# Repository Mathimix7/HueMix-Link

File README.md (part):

<h1 align="center">HueMix-Link</h1>

## Table of Contents

- [Quick Start](#quick-start)
- [Project Overview](#project-overview)
- [Screenshots](#screenshots)
- [What Is In This Repository](#what-is-in-this-repository)
- [System Overview](#system-overview)
- [Prerequisites](#prerequisites)
- [Installation](#installation)
- [First-time Commissioning Workflow](#first-time-commissioning-workflow)
- [ESP Firmware: Build and Flash](#esp-firmware-build-and-flash)
- [Firmware Updates (OTA Page)](#firmware-updates-ota-page)
- [Configuration and Data Storage](#configuration-and-data-storage)
- [Networking and Ports](#networking-and-ports)
- [How Automation Works](#how-automation-works)
- [Devices](#devices)
- [License](#license)

## Quick Start

1. Install the backend on a Linux host:

 ```bash
  git clone https://github.com/Mathimix7/HueMix-Link.git
  cd HueMix-Link
  sudo bash install.sh
  ```

2. Open the web UI at `http://huemixlink.local` or your server IP.
2. Pair your Hue Bridge from the Bridge configuration page.
3. Put an ESP device into pairing mode and add it from the Pairing page.
4. Configure the device behavior, then verify it by triggering a button, motion sensor, or lightstrip sync.

## Project Overview

HueMix-Link is a local smart home bridge that connects custom ESP-based devices (gateways, buttons, remotes, motion sensors, door sensors, and lightstrips) to Philips Hue rooms and scenes.

It provides:

- A Flask web UI for setup and management
- A UDP server for low-latency gateway communication
- Automation logic for buttons, remotes, and motion sensors
- OTA firmware update workflows for all device types
- Backup and restore tools for configuration data

## Screenshots

<table width="85%" align="center">
  <tr>
    <td colspan="2" align="center">
      
    </td>
  </tr>
  <tr>
    <td width="50%" align="center">
      
    </td>
    <td width="50%" align="center">
      
    </td>
  </tr>
  <tr>
    <td width="50%" align="center">
      
    </td>
    <td width="50%" align="center">
      
    </td>
  </tr>
</table>

## What Is In This Repository

- `python/`: Main backend service (Flask UI + UDP network + automations + OTA)
- `esp-firmware/`: PlatformIO firmware sources for all device types (gateway, buttons, remotes, motion sensors, door sensors, lightstrips)
- `Hardware-designs/`: KiCad design files for all device types (gateway, buttons, remotes, motion sensors, door sensors, lightstrips)
- `3D Files/`: 3D model files for all device types (STL format for 3D printing)
- `install.sh`: Linux installer/updater
- `VERSION`: Version file for installer/update workflows

## System Overview

### High-level architecture

1. **All ESP devices use ESP-NOW**: Low-power mesh protocol for device-to-device communication
2. **Gateways bridge ESP-NOW to UDP**: Gateways receive ESP-NOW messages and forward them to the backend via UDP
3. **Backend (UDP server) receives events**: Button presses, remote actions, motion detections, device hellos, delivery reports
4. **Automation engine maps events to Hue actions**: Scene activation, toggle on/off, brightness adjust, and lightstrip sync
5. **Hue state is cached and synchronized**: Automations and lightstrips stay aligned with current room/scene state
6. **Web UI for management**: Device pairing, automation configuration, OTA updates, monitoring, and backups

### Main runtime services

- **Flask + Waitress**: Web UI server `127.0.0.1:5001` (default)
- **UDP listener**: Receives gateway messages on `0.0.0.0:7777` (default, configurable)
- **Automation service**: Listens to device events and Hue state changes, applies configured logic
- **OTA manager**: Handles firmware distribution, chunking, and acknowledgment tracking

## Prerequisites

### Software

- Python 3.9+ (3.10+ recommended)
- `pip` and virtual environment support (`venv`)
- Network access to your Hue Bridge (same LAN)
- Linux OS with `systemd` (for production install)
- `sudo` access and `apt` package manager

### Hardware

- At least one Hue Bridge with configured rooms/scenes
- Supported HueMix-Link devices (gateways, buttons, remotes, motion sensors, door sensors, lightstrips)
- Firmware binaries matching your device type and model

## Installation

### Linux

From the repository root:

```bash
sudo bash install.sh
```

The installer will:

- Deploy the Python app to `/opt/huemix-link`
- Create a dedicated service user and Python virtual environment
- Set up a `systemd` service (`huemix-link`) to run on boot
- Configure HAProxy to expose the web app (HTTP port 80, HTTPS port 443 by default)
- Store all runtime data in `/opt/huemix-link/data`

Useful installer options:

```bash
sudo bash install.sh --help           # Show all options
sudo bash install.sh --yes            # Non-interactive install
sudo bash install.sh --dry-run        # Preview without making changes
sudo bash install.sh --force          # Force recreation of venv
sudo bash install.sh --show-version   # Show installed and source versions
sudo bash install.sh --port 8080      # Expose on custom HTTP port
sudo bash install.sh --no-https       # Disable HTTPS (HTTP only)
sudo bash install.sh --no-local       # Skip huemixlink.local hostname setup
```

After installation, the web UI is accessible at:

- `https://huemixlink.local` (or your server IP)
- `http://huemixlink.local` (or your server IP)

### Updating

To update the backend to a newer version, pull the latest code and re-run the installer:

```bash
git pull
sudo bash install.sh
```

The installer detects the existing installation, updates the files, and restarts the service automatically.

## First-time Commissioning Workflow

1. **Start the backend** (automatic on boot if installed via installer)
2. **Open the web UI** at `http://huemixlink.local` (or your server IP)
3. **Configure Hue Bridge**:
   - Go to the Bridge configuration page
   - Auto-discover or enter bridge IP manually
   - Press the Hue Bridge link button
   - Pair app with bridge (saves credentials)
4. **Pair ESP devices**:
   - Go to Pairing page
   - Start pairing window (choose device type if desired)
   - Power on or reset target devices
   - Devices announce themselves via ESP-NOW → gateway → backend
5. **Configure each device**:
    - **Buttons/Remotes**: Map to room + scenes + action behavior (normal, toggle, brightness, scene-cycle)
    - **Motion Sensors**: Set room, time slots, motion actions, after-actions, cooldown periods
    - **Door Sensors**: Set room, open/close actions, and any automation triggers tied to magnetic state changes
    - **Lightstrips**: Assign room, configure LED count/type, optional color scene overrides
    - **Gateways**: Verify online status, mesh routing, LED schedule (day/night auto-off)
6. **Validate behavior** by triggering physical events and checking Hue room/scene changes

## ESP Firmware: Build and Flash

### Flashing ESP devices

**Option 1: Serial flash via OTA page**

1. Go to the **OTA** page in the web UI
2. Select firmware type
3. Connect ESP device via serial in programming mode
4. Click **Flash** and select serial port
5. Monitor progress on the page

**Option 2: Serial port flash**

Use PlatformIO to flash directly via USB:

```bash
cd esp-firmware
pio run -e esp32_net_node --target upload
```

Or use `esptool.py` directly:

```bash
esptool.py --port /dev/ttyUSB0 write_flash 0x0 huemixlink-esp32-net-vX.Y.Z.bin
```

Pre-built firmware binaries are available in the project's GitHub releases. Download the `.bin` file(s) matching your device type and platform.

## Firmware Updates (OTA Page)

The **OTA** page in the web UI lets you:

- **Check available versions** from GitHub releases
- **Select device** type/model and target device
- **Battery-powered devices**: double-press the reset button before OTA update
- **Initiate flash** with progress monitoring
- **Monitor errors** and retry failed updates

## Configuration and Data Storage

All runtime configuration is stored in `python/data/` (or `/opt/huemix-link/data` in production) as JSON files:

- `bridge.json`: Hue bridge IP and app username
- `config.json`: Server settings (UDP port, dev mode)
- `gateways.json`: Known gateway devices
- `buttons.json`: Button and remote configurations
- `motion_sensors.json`: Motion sensor configurations and time slots
- `lightstrips.json`: Lightstrip configurations and color overrides
- `pairing_history.json`: Last 5 paired devices
- `home_id`: Unique identifier for this HueMix-Link instance. This value is embedded in every packet as a shared secret and used to verify that incoming messages belong to your installation. All devices must be paired while this ID is set — re-pairing is required if it changes.

Backups are created and restored through the settings page; they are stored in `data/backups/`.

## Networking and Ports

- **Web server (internal)**: `127.0.0.1:5001` (Flask)
- **UDP listener (internal)**: `0.0.0.0:7777` (default, receives gateway messages)
- **External HTTP/HTTPS (production)**: Exposed by HAProxy (default HTTP 80 + HTTPS 443)

UDP port can be changed in settings; the backend will restart UDP listening with the new port.

## How Automation Works

1. **Device sends event** via **ESP-NOW** (button press, remote action, motion detection)
2. **Gateway receives** via ESP-NOW and forwards message to backend via **UDP**
3. **UDP server** decodes and validates packet (signature check using HomeID)
4. **Device manager** resolves device identity; **pairing manager** verifies eligibility
5. **Automation engine** applies configured logic:
   - **Buttons/Remotes**: Scene cycle, toggle, brightness adjust, hold-to-adjust
   - **Motion Sensors**: Trigger scenes/lights on detection; post-motion fade/off actions; cooldown throttling
6. **Hue API** is called to apply scene/room/light changes
7. **Hue state manager** caches current room, light, and scene state
8. **Lightstrip sync**: Checks if any lightstrips should mirror current scene; sends raw LED commands via **ESP-NOW → gateway → UDP**

On startup, config sync reconciles saved room/scene references against live Hue topology to avoid stale mappings.

## Devices

### Gateway

<table><tr>
  <td></td>
  <td></td>
</tr></table>

The Gateway is a single board that contains two ESP32 modules working together:

- **Net Node** — connects to your home WiFi and bridges between the backend (UDP) and the ESP-NOW mesh. Runs WiFiManager for wireless configuration and relays commands to the radio node over a high-speed UART link.
- **Radio Node** — handles all ESP-NOW communication with peripheral devices (buttons, remotes, sensors, lightstrips) and forwards packets to/from the net node over UART. Extends ESP-NOW coverage independently of WiFi.

**LED indicators**

| LED | State | Meaning |
|-----|-------|---------|
| WiFi | Off | No power / booting |
| WiFi | Fast blink (0.2s) | Not yet configured — WiFi config portal is open |
| WiFi | Slow blink (0.5s) | Connecting or retrying WiFi |
| WiFi | Solid on | Online and operational |
| Data | Brief flash | Packet received or forwarded |
| Data | Breathing (fade in/out) | Net node OTA firmware update in progress |
| Radio | Brief flash | ESP-NOW packet relayed |
| Radio | Breathing (fade in/out) | Radio node OTA firmware update in progress |

**Buttons**

- **Main button**: Acts as a single button that can be mapped to a Hue room in the web UI
- **Aux button**: Hold 5+ seconds to factory-reset and re-open the WiFi config portal

**Initial setup**

1. Power on the gateway — the WiFi LED fast-blinks and it broadcasts SSID `HueMix Link - XXXXXXXX`
2. Connect to that SSID (password: `HueMixLink`) with a phone or laptop
3. Enter your home WiFi credentials and the backend server IP + UDP port
4. The gateway connects, the WiFi LED goes solid, and it sends a HELLO to the backend

**Pairing**

Gateways pair automatically once configured.

**OTA**

Both nodes are updated from the OTA page. Gateways receive OTA directly (no double-press needed).

---

### Radio Gateway (Serial Python)

The Radio Gateway can also run as a serial-connected ESP32 node that pairs with the Python backend instead of WiFi.

- **Net/host side**: Python maintains the gateway state, serial transport, OTA scheduling, and dashboard telemetry
- **Radio side**: ESP32 radio node handles ESP-NOW traffic, OLED status display, and forwards packets over UART
- **LED indicators**: Follows the configured gateway LED schedule; the OLED display also respects the same on/off timing
- **OTA**: Updated from the OTA page using the `gateway_radio_python` firmware target

**Setup**

1. Flash the `esp32_radio_python` firmware
2. Connect the radio node to the backend host over USB serial
3. Configure the serial port in the web UI
4. The backend will sync HOME_ID, gateway state, and dashboard telemetry automatically

---

### Button

<table><tr>
  <td></td>
  <td></td>
</tr></table>

The Button is a single pushbutton device that sends click, hold, and release events via ESP-NOW. The ESP32 version is battery-powered and deep-sleeps between presses, while the ESP8266 version is always-on and runs continuously.

> [!WARNING]
> The `normal_button` firmware is deprecated. The ESP32 Normal Button board v3 and later should use the `remote_button` firmware configured as 1, 2, or 3 buttons.

**Events sent**

| Action | Trigger |
|--------|---------|
| Click | Short press and release |
| Holding | Held beyond 500 ms, repeated every 500 ms |
| Release | Released after a hold |

**Default automation** (configurable in web UI): Click cycles scenes in the assigned room. Hold adjusts brightness. Release stops brightness adjustment.

**LED indicators**

| State | Meaning |
|-------|---------|
| Brief flash | Action sent via ESP-NOW |
| 2 fast blinks | No acknowledgment — gateway may be out of range |
| 2 slow blinks | Failed to pair device |
| 3 blinks | OTA mode |
| 5 blinks | Device powered on |
| Breathing | OTA in progress |

**Setup and pairing**

1. Flash firmware via serial or the OTA page
2. Open the Pairing page, start a pairing window, then press the button to wake the device
3. After pairing, assign the button to a room in the device settings

**OTA**

**Double-press the reset button** to enter OTA mode — the LED will blink 3 times to confirm. Then initiate the flash from the OTA page.

---

### Remote

<table><tr>
  <td></td>
  <td></td>
</tr></table>

The Remote is a battery-powered ESP32 device with up to 4 independently configurable buttons. Each button can target a different room with its own action type. The number of active buttons (1–4) is configured via hardware at flash time.

**Action types per button** (configurable in web UI)

| Type | Click | Hold |
|------|-------|------|
| Normal | Cycle scenes / turn room off | Adjust brightness |
| Toggle | Toggle room on/off | — |
| Brightness Up | Increase brightness | Increase continuously |
| Brightness Down | Decrease brightness | Decrease continuously |
| Scene Cycle | Cycle scenes (no off) | Adjust brightness |

**LED indicators**

| State | Meaning |
|-------|---------|
| Brief flash | Button action sent |
| 2 fast blinks | No acknowledgment — gateway may be out of range |
| 2 slow blinks | Failed to pair device |
| 3 blinks | OTA mode |
| 5 blinks | Device powered on |
| On 2 seconds | Button count configuration saved |
| Breathing | OTA in progress |

**Setting the button count**

Triple-press the reset button within 1 second to enter button-count config mode, while holding the target number of buttons simultaneously:

- 1 button: hold only button 4
- 2 buttons: hold buttons 1 + 2
- 3 buttons: hold buttons 1 + 2 + 4
- 4 buttons: hold all four buttons or None

**Setup and pairing**

1. Flash firmware via serial or the OTA page
2. Open the Pairing page, start a pairing window, then press any button to wake the device
3. After pairing, configure each button's room and action type in the device settings

**OTA**

Battery-powered. **Double-press the reset button** to enter OTA mode. The LED will blink 3 times to confirm. Then flash from the OTA page.

---

### Motion Sensor

<table><tr>
  <td></td>
  <td></td>
</tr></table>

The Motion Sensor is a battery-powered ESP32 device with a PIR sensor and an ambient light level sensor (LDR). It sleeps in deep sleep and wakes when the PIR fires. After sending a motion event it enters a configurable cooldown period (default 60s) before re-arming.

**Data sent on motion detection**

- Motion detected flag
- Ambient light level (1-10)
- Battery voltage

**LED indicators**

| State | Meaning |
|-------|---------|
| Brief flash | Motion detected, event sent |
| 2 fast blinks | No acknowledgment — gateway may be out of range |
| 3 blinks | OTA mode |
| 5 blinks | Device powered on |
| Breathing | OTA in progress |

**Automation options** (configurable in web UI)

- Assign to a room and one or more scenes
- Set time slots (e.g., a different scene during the night)
- Configure an after-motion action (turn off, dim, change scene) and its delay
- Set the cooldown period (minimum seconds before re-triggering)

**Setup and pairing**

1. Flash firmware via serial or the OTA page
2. Open the Pairing page, start a pairing window, then single-press the reset button to wake the device
3. After pairing, configure the room, scenes, and time slots in the device settings

**OTA**

Battery-powered. **Double-press the reset button** to enter OTA mode. The LED will blink 3 times to confirm. Then flash from the OTA page.

---

### Door Sensor

<table><tr>
  <td></td>
  <td></td>
</tr></table>

The Door Sensor is a battery-powered ESP32 device that reports magnetic open/close state changes and ambient light level over ESP-NOW.

**Events sent**

- Door opened
- Door closed
- Ambient light level (1-10)
- Battery voltage
- Firmware version / platform metadata

**LED indicators**

| State | Meaning |
|-------|---------|
| Brief flash | Door event sent |
| 2 fast blinks | No acknowledgment — gateway may be out of range |
| 3 blinks | OTA mode |
| 5 blinks | Device powered on |
| Breathing | OTA in progress |

**Setup and pairing**

1. Flash the door sensor firmware via serial or the OTA page
2. Open the Pairing page, start a pairing window, then single-press the reset button or activate the reed switch to wake the device
3. After pairing, assign the sensor to a room and add any open/close automations

**OTA**

Battery-powered. **Double-press the reset button** to enter OTA mode. Then flash from the OTA page.

---

### Lightstrip

<table><tr>
  <td></td>
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
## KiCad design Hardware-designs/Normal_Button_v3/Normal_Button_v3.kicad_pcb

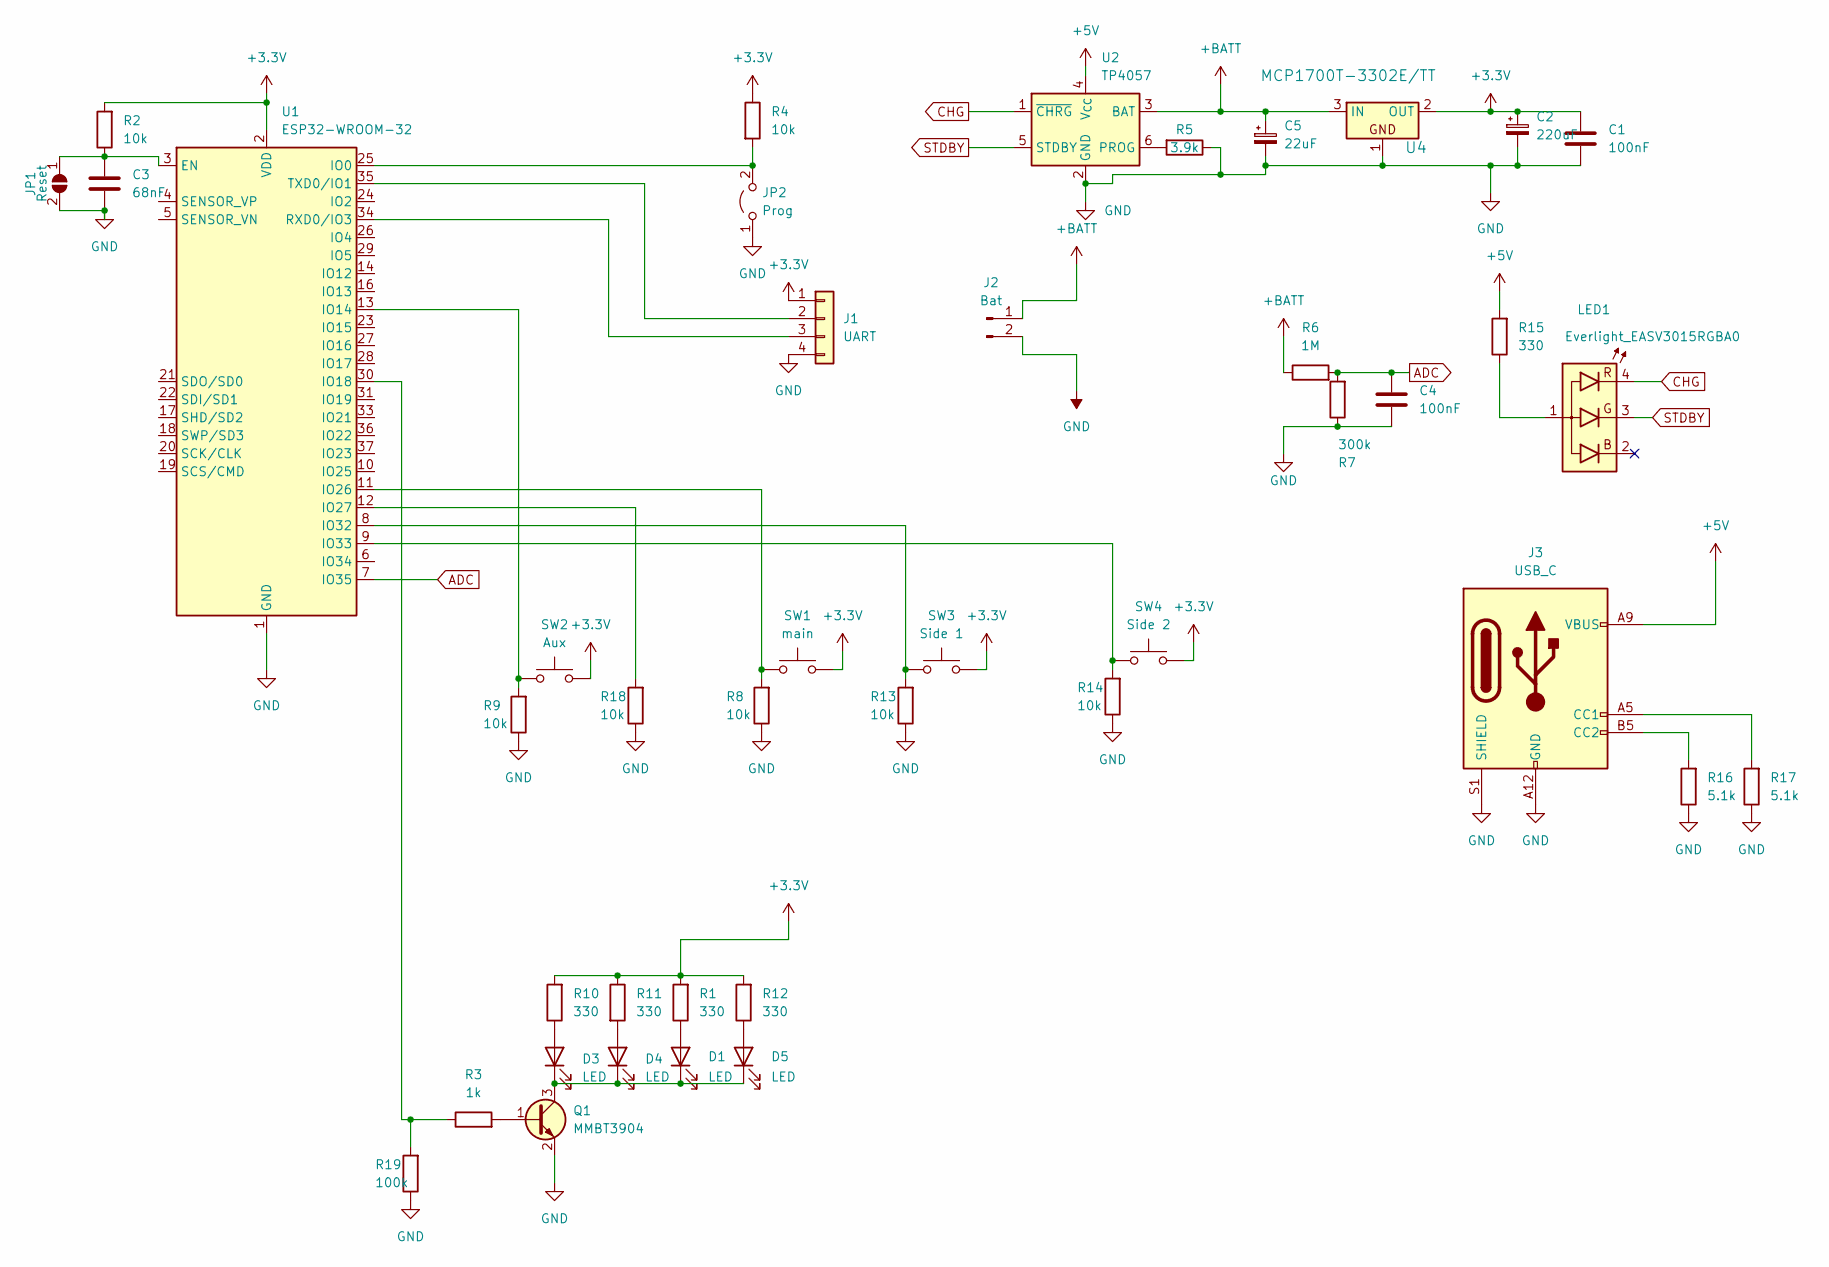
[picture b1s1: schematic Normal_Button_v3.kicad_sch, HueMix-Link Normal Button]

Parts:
C1, C4: 100nF; C_0805_2012Metric_Pad1.18x1.45mm_HandSolder
C2: 220uF; CP_EIA-6032-15_Kemet-U_HandSolder
C3: 68nF; C_0805_2012Metric_Pad1.18x1.45mm_HandSolder
C5: 22uF; CP_EIA-6032-15_Kemet-U_HandSolder
D1, D3, D4, D5: LED; LED_D3.0mm
J1: UART; PinHeader_1x04_P2.54mm_Vertical
J2: Bat; JST_EH_B2B-EH-A_1x02_P2.50mm_Vertical
J3: USB_C; USB_C_Receptacle_GCT_USB4125-xx-x-0190_6P_TopMnt_Horizontal
JP1: Reset; SolderJumper-2_P1.3mm_Open_Pad1.0x1.5mm
JP2: Prog; PinHeader_1x02_P2.54mm_Vertical
LED1: Everlight_EASV3015RGBA0; LED_D5.0mm-4_RGB
Q1: MMBT3904; SOT-23
R1, R10, R11, R12, R15: 330; R_1206_3216Metric_Pad1.30x1.75mm_HandSolder
R2, R4, R8, R9, R13, R14, R18: 10k; R_1206_3216Metric_Pad1.30x1.75mm_HandSolder
R3: 1k; R_1206_3216Metric_Pad1.30x1.75mm_HandSolder
R5: 3.9k; R_1206_3216Metric_Pad1.30x1.75mm_HandSolder
R6: 1M; R_1206_3216Metric_Pad1.30x1.75mm_HandSolder
R7: 300k; R_1206_3216Metric_Pad1.30x1.75mm_HandSolder
R16, R17: 5.1k; R_1206_3216Metric_Pad1.30x1.75mm_HandSolder
R19: 100k; R_1206_3216Metric_Pad1.30x1.75mm_HandSolder
SW1: main; SW_PUSH-12mm
SW2: Aux; SW_PUSH_6mm
SW3: Side 1; SW_PUSH-12mm
SW4: Side 2; SW_PUSH-12mm
U1: ESP32-WROOM-32; ESP32-WROOM-32E
U2: TP4057; TSOT-23-6_HandSoldering
U4: MCP1700T-3302E/TT; SOT-23

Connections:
+3.3V: C1.1, C2.1, J1.1, R1.2, R2.2, R4.1, R10.2, R11.1, R12.2, SW1.2, SW2.2, SW3.2, SW4.2, U1.2 (VDD), U4.2 (OUT)
+5V: J3.A9 (VBUS), J3.B9 (VBUS), R15.2, U2.4 (V_{CC})
+BATT: C5.1, J2.1, R6.1, U2.3 (BAT), U4.3 (IN)
ADC: C4.1, R6.2, R7.2, U1.7 (IO35)
CHG: LED1.4 (R), U2.1 (~CHRG)
GND: C1.2, C2.2, C3.2, C4.2, C5.2, J1.4, J2.2, J3.A12 (GND), J3.B12 (GND), J3.S1 (SHIELD), JP1.2 (B), JP2.1 (A), Q1.2 (E), R5.1, R7.1, R8.1, R9.1, R13.1, R14.1, R16.1, R17.1, R18.1, R19.1, U1.1 (GND), U1.15 (GND), U1.38 (GND), U1.39 (GND), U2.2 (GND), U4.1
unnamed: D1.2 (A), R1.1
unnamed: D1.1 (K), D3.1 (K), D4.1 (K), D5.1 (K), Q1.3 (C)
unnamed: D3.2 (A), R10.1
unnamed: D4.2 (A), R11.2
unnamed: D5.2 (A), R12.1
unnamed: J1.2, U1.35 (TXD0/IO1)
unnamed: J1.3, U1.34 (RXD0/IO3)
unnamed: J3.A5 (CC1), R17.2
unnamed: J3.B5 (CC2), R16.2
unnamed: C3.1, JP1.1 (A), R2.1, U1.3 (EN)
unnamed: JP2.2 (B), R4.2, U1.25 (IO0)
unnamed: LED1.1 (A), R15.1
unnamed: Q1.1 (B), R3.2
unnamed: R9.2, SW2.1, U1.13 (IO14)
unnamed: R3.1, R19.2, U1.30 (IO18)
unnamed: R8.2, SW1.1, U1.11 (IO26)
unnamed: R18.2, U1.12 (IO27)
unnamed: R13.2, SW3.1, U1.8 (IO32)
unnamed: R14.2, SW4.1, U1.9 (IO33)
unnamed: R5.2, U2.6 (PROG)
STDBY: LED1.3 (G), U2.5 (STDBY)

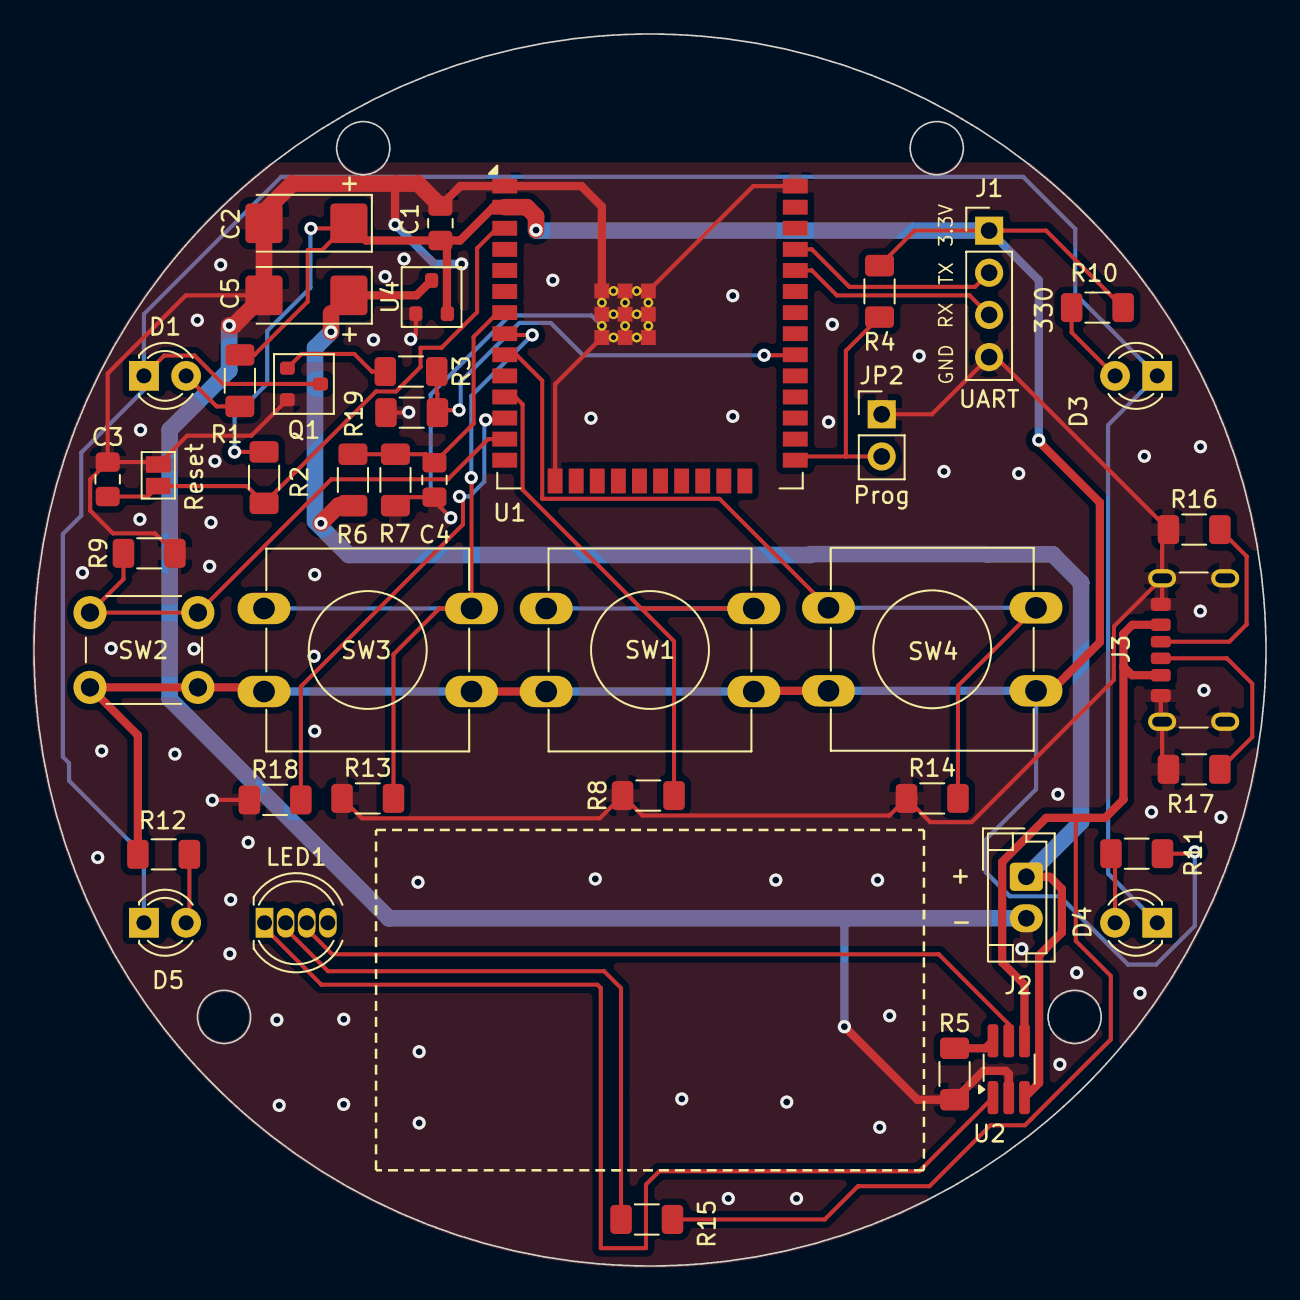
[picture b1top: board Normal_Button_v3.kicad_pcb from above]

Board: 2 copper layers, 74.2 x 74.2 mm, 42 parts (0 on the bottom side), 27 nets.

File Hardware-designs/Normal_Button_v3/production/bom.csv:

Designator,Footprint,Quantity,Value,LCSC Part #
"C1, C4",0805,2,100nF,
C2,CP_EIA-6032-15_Kemet-U_HandSolder,1,220uF,
C3,0805,1,68nF,
C5,CP_EIA-6032-15_Kemet-U_HandSolder,1,22uF,
"D1, D3, D4, D5",LED_D3.0mm,4,LED,
J1,PinHeader_1x04_P2.54mm_Vertical,1,UART,
J2,JST_EH_B2B-EH-A_1x02_P2.50mm_Vertical,1,Bat,
J3,USB_C_Receptacle_GCT_USB4125-xx-x-0190_6P_TopMnt_Horizontal,1,USB_C,
JP1,SolderJumper-2_P1.3mm_Open_Pad1.0x1.5mm,1,Reset,
JP2,PinHeader_1x02_P2.54mm_Vertical,1,Prog,
LED1,LED_D5.0mm-4_RGB,1,Everlight_EASV3015RGBA0,
Q1,SOT-23,1,MMBT3904,
"R1, R10, R11, R12, R15",1206,5,330,
"R13, R14, R18, R2, R4, R8, R9",1206,7,10k,
"R16, R17",1206,2,5.1k,
R19,1206,1,100k,
R3,1206,1,1k,
R5,1206,1,3.9k,
R6,1206,1,1M,
R7,1206,1,300k,
SW1,SW_PUSH-12mm,1,main,
SW2,SW_PUSH_6mm,1,Aux,
SW3,SW_PUSH-12mm,1,Side 1,
SW4,SW_PUSH-12mm,1,Side 2,
U1,ESP32-WROOM-32E,1,ESP32-WROOM-32,
U2,TSOT-23-6_HandSoldering,1,TP4057,
U4,SOT-23,1,MCP1700T-3302E/TT,

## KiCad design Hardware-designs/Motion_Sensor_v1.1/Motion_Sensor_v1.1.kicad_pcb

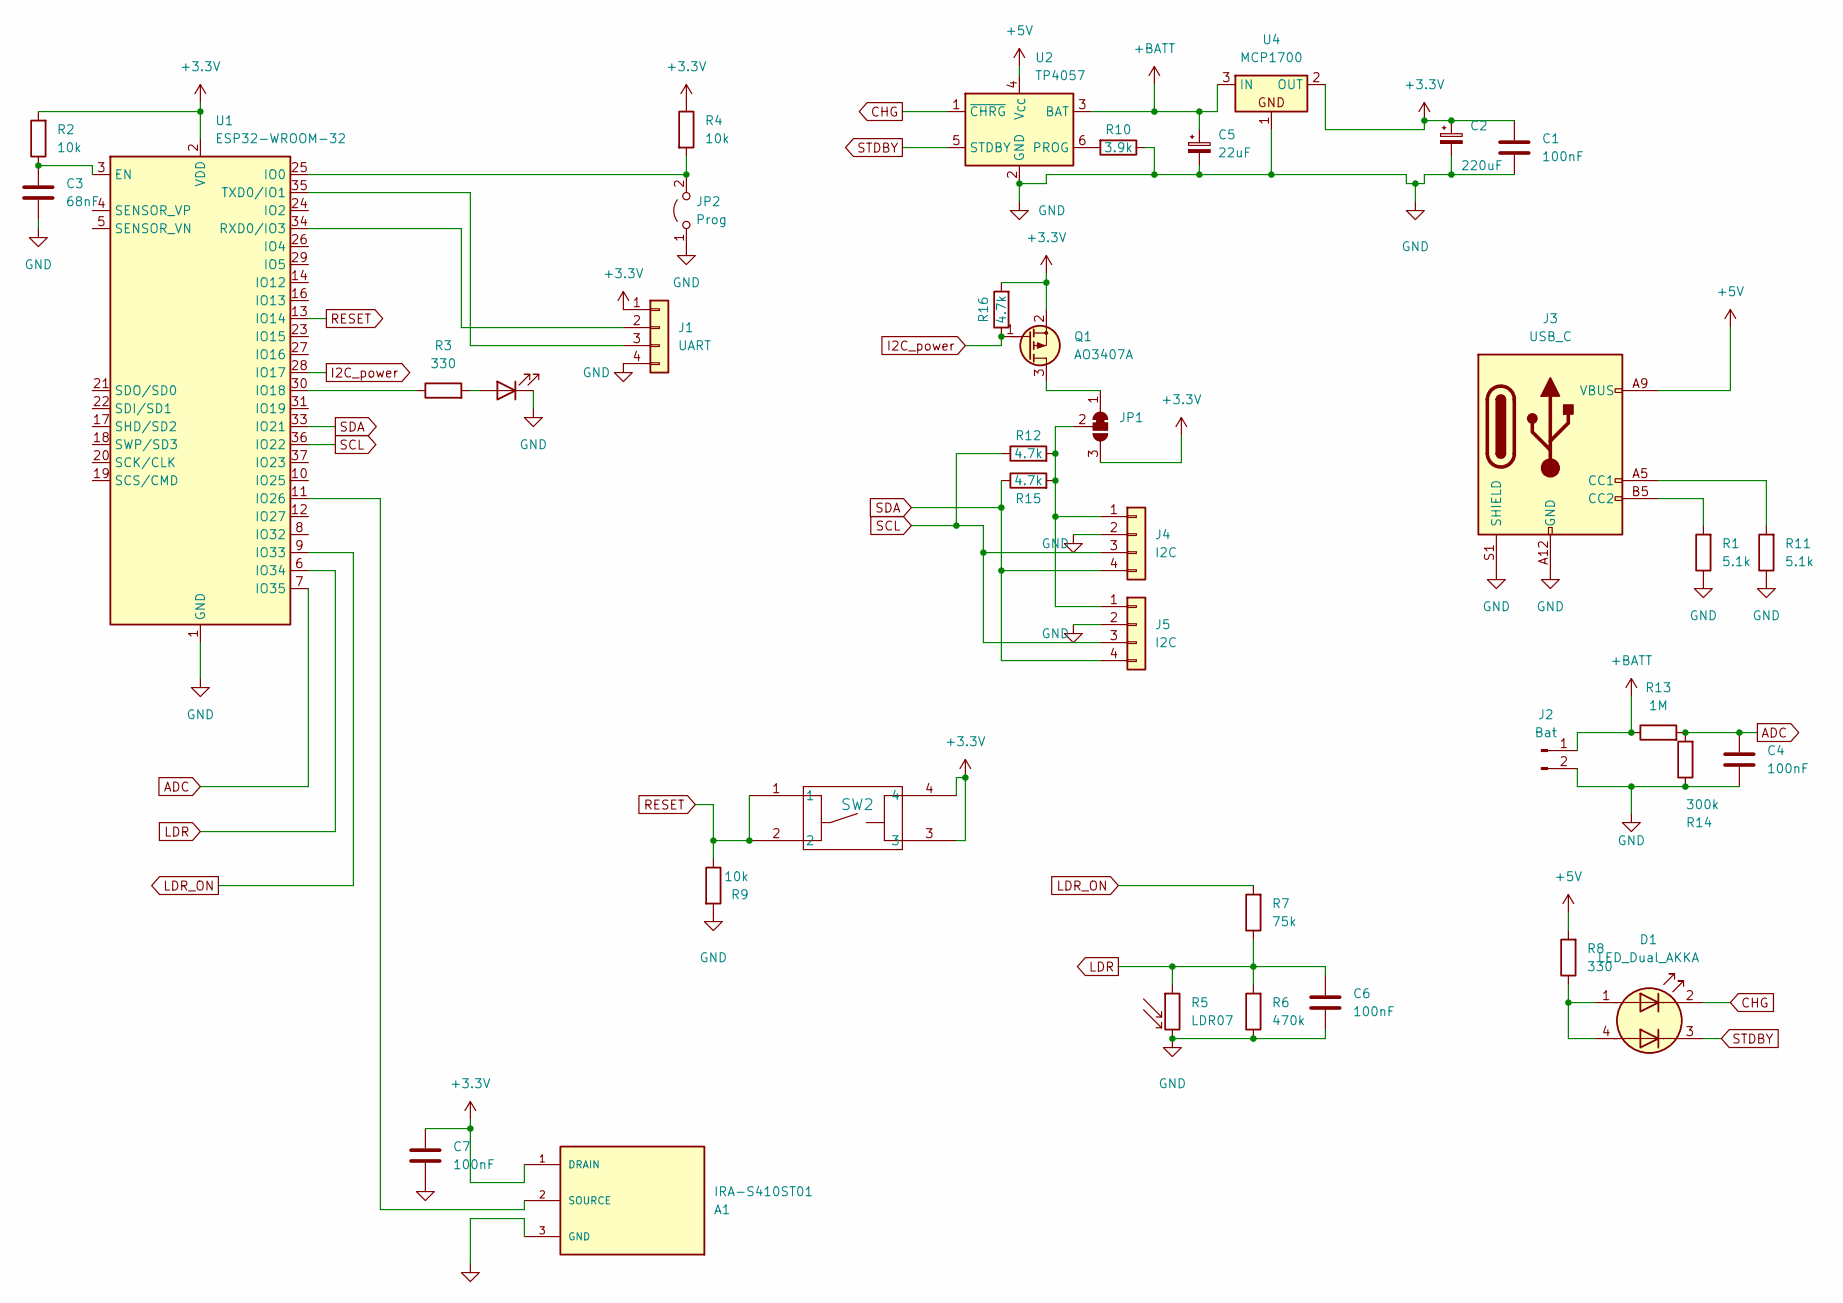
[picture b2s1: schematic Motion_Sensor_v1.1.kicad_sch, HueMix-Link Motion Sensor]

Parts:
A1: IRA-S410ST01; TO254P940H490-3
C1, C4, C6, C7: 100nF; C_0805_2012Metric_Pad1.18x1.45mm_HandSolder
C2: 220uF; CP_EIA-6032-15_Kemet-U_HandSolder
C3: 68nF; C_0805_2012Metric_Pad1.18x1.45mm_HandSolder
C5: 22uF; CP_EIA-6032-15_Kemet-U_HandSolder
D1: LED_Dual_AKKA; APHBM2012ETSGTC
D3: LED; LED_1206_3216Metric
J1: UART; PinHeader_1x04_P2.54mm_Vertical
J2: Bat; TestPoint_2Pads_Pitch2.54mm_Drill0.8mm
J3: USB_C; USB_C_Receptacle_GCT_USB4125-xx-x-0190_6P_TopMnt_Horizontal
J4, J5: I2C; PinHeader_1x04_P2.54mm_Vertical
JP1: SolderJumper_3_Bridged12; SolderJumper-3_P1.3mm_Bridged12_RoundedPad1.0x1.5mm
JP2: Prog; PinHeader_1x02_P2.54mm_Vertical
Q1: AO3407A; SOT-23
R1, R11: 5.1k; R_1206_3216Metric_Pad1.30x1.75mm_HandSolder
R2, R4, R9: 10k; R_1206_3216Metric_Pad1.30x1.75mm_HandSolder
R3, R8: 330; R_1206_3216Metric_Pad1.30x1.75mm_HandSolder
R5: LDR07; R_LDR_5.1x4.3mm_P3.4mm_Vertical
R6: 470k; R_1206_3216Metric_Pad1.30x1.75mm_HandSolder
R7: 75k; R_1206_3216Metric_Pad1.30x1.75mm_HandSolder
R10: 3.9k; R_1206_3216Metric_Pad1.30x1.75mm_HandSolder
R12, R15, R16: 4.7k; R_1206_3216Metric_Pad1.30x1.75mm_HandSolder
R13: 1M; R_1206_3216Metric_Pad1.30x1.75mm_HandSolder
R14: 300k; R_1206_3216Metric_Pad1.30x1.75mm_HandSolder
SW2: PTS526 SM15 SMTR2 LFS; SMT_FS
U1: ESP32-WROOM-32; ESP32-WROOM-32D
U2: TP4057; TSOT-23-6_HandSoldering
U4: MCP1700; SOT-23

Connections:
+3.3V: A1.1 (DRAIN), C1.1, C2.1, C7.1, J1.1, JP1.3 (B), Q1.2 (S), R2.2, R4.1, R16.2, SW2.3, SW2.4, U1.2 (VDD), U4.2 (OUT)
+5V: J3.A9 (VBUS), J3.B9 (VBUS), R8.2, U2.4 (V_{CC})
+BATT: C5.1, J2.1, R13.1, U2.3 (BAT), U4.3 (IN)
ADC: C4.1, R13.2, R14.2, U1.7 (IO35)
CHG: D1.2 (K1), U2.1 (~CHRG)
GND: A1.3 (GND), C1.2, C2.2, C3.2, C4.2, C5.2, C6.2, C7.2, D3.1 (K), J1.4, J2.2, J3.A12 (GND), J3.B12 (GND), J3.S1 (SHIELD), J4.2, J5.2, JP2.1 (A), R1.1, R5.2, R6.1, R9.2, R10.1, R11.1, R14.1, U1.1 (GND), U1.15 (GND), U1.38 (GND), U1.39 (GND), U2.2 (GND), U4.1
I2C_power: Q1.1 (G), R16.1, U1.28 (IO17)
LDR: C6.1, R5.1, R6.2, R7.1, U1.6 (IO34)
LDR_ON: R7.2, U1.9 (IO33)
unnamed: A1.2 (SOURCE), U1.11 (IO26)
unnamed: D1.1 (A1), D1.4 (A2), R8.1
unnamed: D3.2 (A), R3.2
unnamed: J1.2, U1.34 (RXD0/IO3)
unnamed: J1.3, U1.35 (TXD0/IO1)
unnamed: J3.A5 (CC1), R11.2
unnamed: J3.B5 (CC2), R1.2
unnamed: J4.1, J5.1, JP1.2 (C), R12.2, R15.2
unnamed: JP1.1 (A), Q1.3 (D)
unnamed: JP2.2 (B), R4.2, U1.25 (IO0)
unnamed: C3.1, R2.1, U1.3 (EN)
unnamed: R3.1, U1.30 (IO18)
unnamed: R10.2, U2.6 (PROG)
RESET: R9.1, SW2.1, SW2.2, U1.13 (IO14)
SCL: J4.3, J5.3, R12.1, U1.36 (IO22)
SDA: J4.4, J5.4, R15.1, U1.33 (IO21)
STDBY: D1.3 (K2), U2.5 (STDBY)

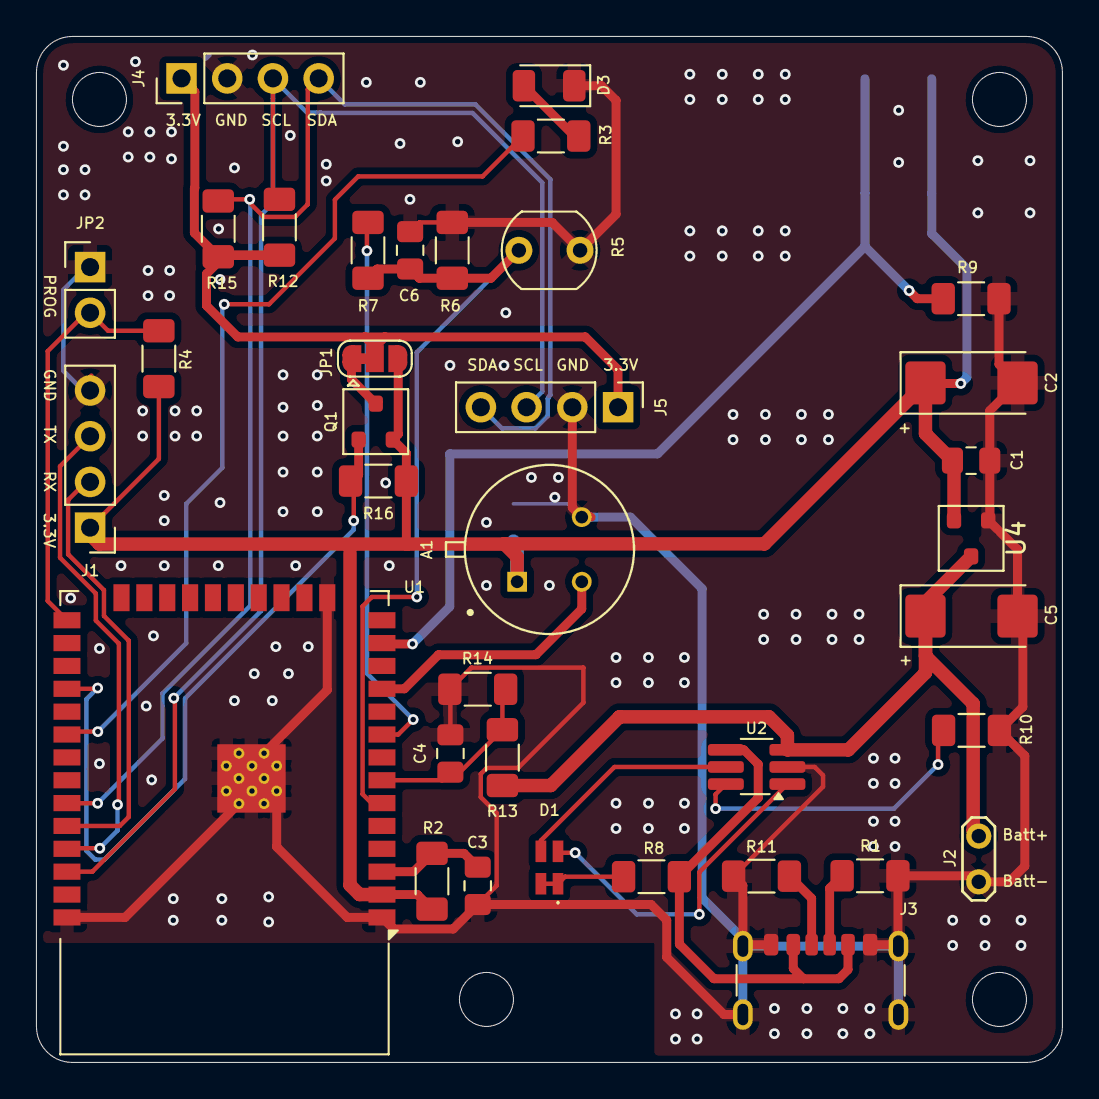
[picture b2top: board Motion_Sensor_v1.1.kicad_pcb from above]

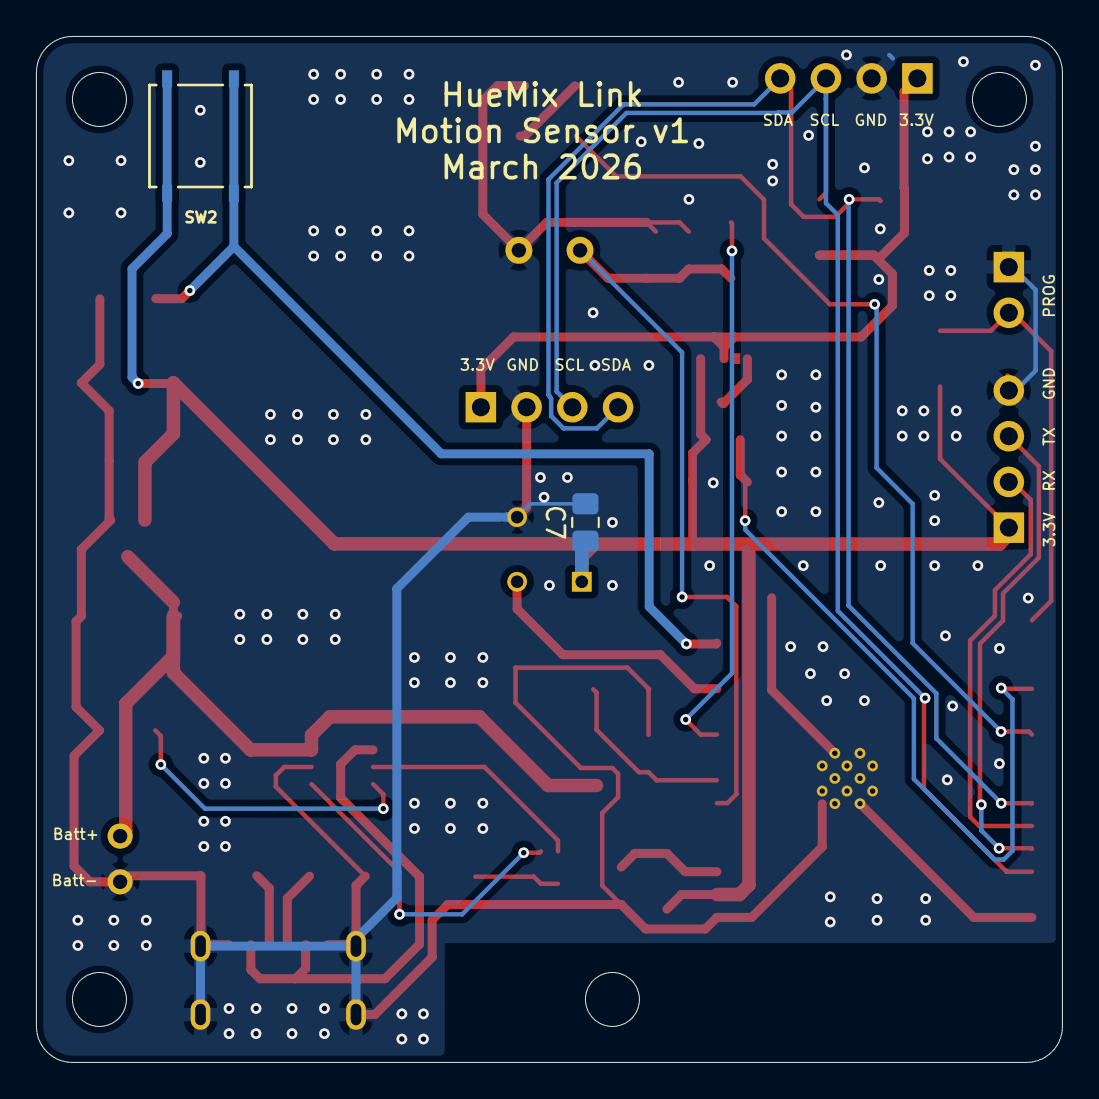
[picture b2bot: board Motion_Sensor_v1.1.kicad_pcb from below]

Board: 2 copper layers, 57.0 x 57.0 mm, 38 parts (2 on the bottom side), 26 nets.

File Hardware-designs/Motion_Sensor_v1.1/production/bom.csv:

Designator,Footprint,Quantity,Value,LCSC Part #
A1,TO254P940H490-3,1,IRA-S410ST01,
"C1, C4, C6",0805,3,100nF,
C2,CP_EIA-6032-15_Kemet-U_HandSolder,1,220uF,
C3,0805,1,68nF,
C5,CP_EIA-6032-15_Kemet-U_HandSolder,1,22uF,
D1,APHBM2012ETSGTC,1,LED_Dual_AKKA,
D3,1206,1,LED,
J1,PinHeader_1x04_P2.54mm_Vertical,1,UART,
J2,TestPoint_2Pads_Pitch2.54mm_Drill0.8mm,1,Bat,
J3,USB_C_Receptacle_GCT_USB4125-xx-x-0190_6P_TopMnt_Horizontal,1,USB_C,
"J4, J5",PinHeader_1x04_P2.54mm_Vertical,2,I2C,
JP2,PinHeader_1x02_P2.54mm_Vertical,1,Prog,
Q1,SOT-23,1,AO3407A,
"R1, R11",1206,2,5.1k,
R10,1206,1,3.9k,
"R12, R15, R16",1206,3,4.7k,
R13,1206,1,1M,
R14,1206,1,300k,
"R2, R4, R9",1206,3,10k,
"R3, R8",1206,2,330,
R5,R_LDR_5.1x4.3mm_P3.4mm_Vertical,1,LDR07,
R6,1206,1,470k,
R7,1206,1,75k,
SW2,SMT_FS,1,PTS526 SM15 SMTR2 LFS,
U1,ESP32-WROOM-32D,1,ESP32-WROOM-32,
U2,TSOT-23-6_HandSoldering,1,TP4057,
U4,SOT-23,1,MCP1700,

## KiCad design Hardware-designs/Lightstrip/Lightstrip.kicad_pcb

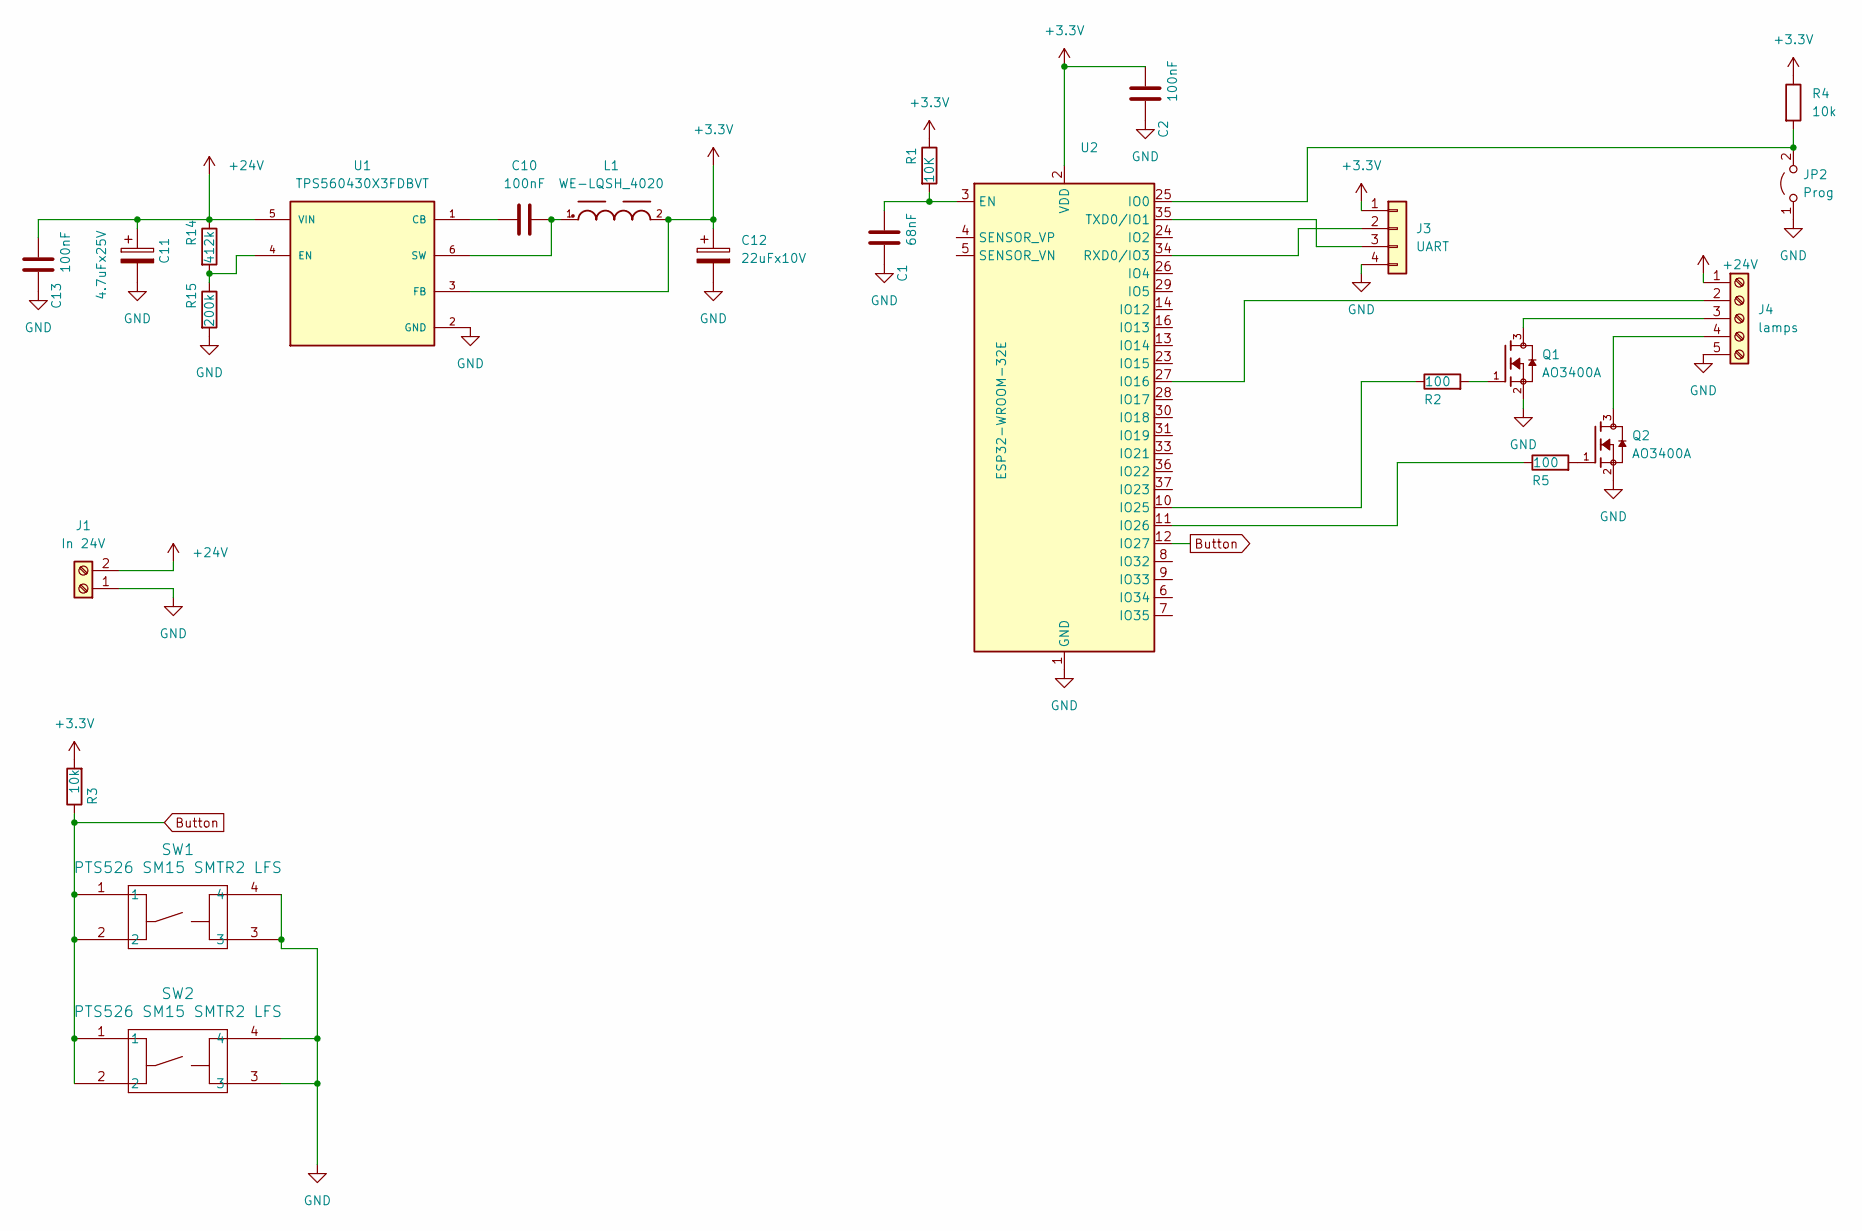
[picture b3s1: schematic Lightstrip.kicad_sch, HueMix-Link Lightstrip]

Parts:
C1: 68nF; C_0603_1608Metric_Pad1.08x0.95mm_HandSolder
C2, C10, C13: 100nF; C_0603_1608Metric_Pad1.08x0.95mm_HandSolder
C11: 4.7uFx25V; C_1206_3216Metric_Pad1.33x1.80mm_HandSolder
C12: 22uFx10V; C_1206_3216Metric_Pad1.33x1.80mm_HandSolder
J1: In 24V; TerminalBlock_MaiXu_MX126-5.0-02P_1x02_P5.00mm
J3: UART; PinHeader_1x04_P2.54mm_Vertical
J4: lamps; TerminalBlock_MaiXu_MX126-5.0-05P_1x05_P5.00mm
JP2: Prog; PinHeader_1x02_P2.54mm_Vertical
L1: WE-LQSH_4020
Q1, Q2: AO3400A; SOT95P280X125-3N; PARTREV L
R1: 10K; R_1206_3216Metric_Pad1.30x1.75mm_HandSolder
R2, R5: 100; R_1206_3216Metric_Pad1.30x1.75mm_HandSolder
R3, R4: 10k; R_1206_3216Metric_Pad1.30x1.75mm_HandSolder
R14: 412k; R_1206_3216Metric_Pad1.30x1.75mm_HandSolder
R15: 200k; R_1206_3216Metric_Pad1.30x1.75mm_HandSolder
SW1, SW2: PTS526 SM15 SMTR2 LFS; SMT_FS
U1: TPS560430X3FDBVT; IC_TPS560430X3FDBVT; PARTREV B
U2: ESP32-WROOM-32E; ESP32-WROOM-32D

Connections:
+3.3V: C2.2, C12.1, J3.1, L1.2, R1.1, R3.2, R4.1, U1.3 (FB), U2.2 (VDD)
+24V: C11.1, C13.2, J1.2, J4.1, R14.1, U1.5 (VIN)
Button: R3.1, SW1.1, SW1.2, SW2.1, SW2.2, U2.12 (IO27)
GND: C1.1, C2.1, C11.2, C12.2, C13.1, J1.1, J3.4, J4.5, JP2.1 (A), Q1.2, Q2.2, R15.2, SW1.3, SW1.4, SW2.3, SW2.4, U1.2 (GND), U2.1 (GND), U2.15 (GND), U2.38 (GND), U2.39 (GND)
unnamed: J3.2, U2.34 (RXD0/IO3)
unnamed: J3.3, U2.35 (TXD0/IO1)
unnamed: J4.2, U2.27 (IO16)
unnamed: J4.3, Q1.3
unnamed: J4.4, Q2.3
unnamed: JP2.2 (B), R4.2, U2.25 (IO0)
unnamed: Q1.1, R2.2
unnamed: Q2.1, R5.2
unnamed: C10.1, U1.1 (CB)
unnamed: R14.2, R15.1, U1.4 (EN)
unnamed: C10.2, L1.1, U1.6 (SW)
unnamed: C1.2, R1.2, U2.3 (EN)
unnamed: R2.1, U2.10 (IO25)
unnamed: R5.1, U2.11 (IO26)

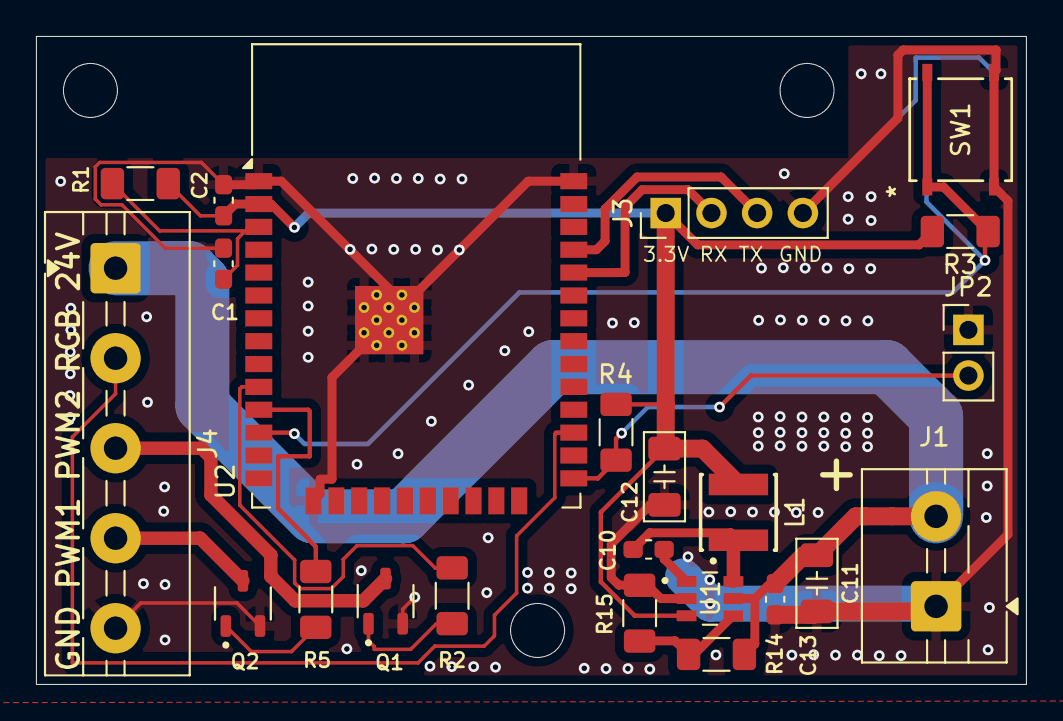
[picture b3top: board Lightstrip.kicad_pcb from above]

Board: 2 copper layers, 55.0 x 36.0 mm, 24 parts (1 on the bottom side), 18 nets.

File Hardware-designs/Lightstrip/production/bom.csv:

Designator,Footprint,Quantity,Value,LCSC Part #
C1,0603,1,68nF,
"C10, C13, C2",0603,3,100nF,
C11,1206,1,4.7uFx25V,
C12,1206,1,22uFx10V,
J1,TerminalBlock_MaiXu_MX126-5.0-02P_1x02_P5.00mm,1,In 24V,
J3,PinHeader_1x04_P2.54mm_Vertical,1,UART,
J4,TerminalBlock_MaiXu_MX126-5.0-05P_1x05_P5.00mm,1,lamps,
JP2,PinHeader_1x02_P2.54mm_Vertical,1,Prog,
L1,WE-LQSH_4020,1,WE-LQSH_4020,
"Q1, Q2",SOT95P280X125-3N,2,AO3400A,
"R1, R3, R4",1206,3,10K,
R14,1206,1,412k,
R15,1206,1,200k,
"R2, R5",1206,2,100,
"SW1, SW2",SMT_FS,2,PTS526 SM15 SMTR2 LFS,
U1,IC_TPS560430X3FDBVT,1,TPS560430X3FDBVT,
U2,ESP32-WROOM-32D,1,ESP32-WROOM-32E,

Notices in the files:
README.md:
This project is licensed under the terms in `LICENSE`.
